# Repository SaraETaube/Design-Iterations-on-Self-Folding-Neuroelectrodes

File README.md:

# Design-Iterations-on-Self-Folding-Neuroelectrodes

The following files have been made available: 
- Project Report: Sara Taube_Design Iterations on Neuroelectrodes.pdf
- Project Poster: Sara Taube_final poster.pdf
- Project files:
    1. Electrode Design Files: in 1-electrode_design >
       final electrode slider.stl : printing file for electrode
       final electrode slider-SAP.stl : printing file for the SAP on electrode
       final electrode.ipt : Autodesk Inventor project file
    2. Applicator Design Files: in 2-surgical_implantation >
       hook_applicator_slide in.stl : printing file for applicator
       hook_applicator_slide in.ipt : Autodesk Inventor project file for applicator
       5 nerve model
       >  5 nerve model.stl : printing file for nerve model
       >  5 nerve model.ipt : Autodesk Inventor project file for nerve model
    3. Flexible Tether Design Files: in 3-flexible_tethers >
       long flex with bend : folder for KiCad Project files
       short flex with bend : folder for KiCad Project files
       spiral flex : folder for KiCad Project files
    4. Additional Design Files I created for Lukas during the internship: in 4-additional_stuff >
       fpc_connector_18pinOmnetics : folder for KiCad Project files for a connector PCB FPC-18pin Omnetics
       fpc_connector_36pinOmnetics : folder for KiCad Project files for a connector PCB FPC-36pin Omnetics
       Glas_Fiber_PCB : folder for KiCad Project files for a separate glas fiber project Lukas was doing
       USB_18pinOmnetics_bend : folder for KiCad Project files for a connector PCB USB-18pin Omnetics; bend for spacial efficacy
       USB_36pinOmnetics_straight : folder for KiCad Project files for a connector PCB USB-18pin Omnetics; no bend
       USB_18pinOmnetics_bend : folder for KiCad Project files for a connector PCB USB-36pin Omnetics; bend for spacial efficacy
       USB_36pinOmnetics_straight : folder for KiCad Project files for a connector PCB USB-36pin Omnetics; no bend

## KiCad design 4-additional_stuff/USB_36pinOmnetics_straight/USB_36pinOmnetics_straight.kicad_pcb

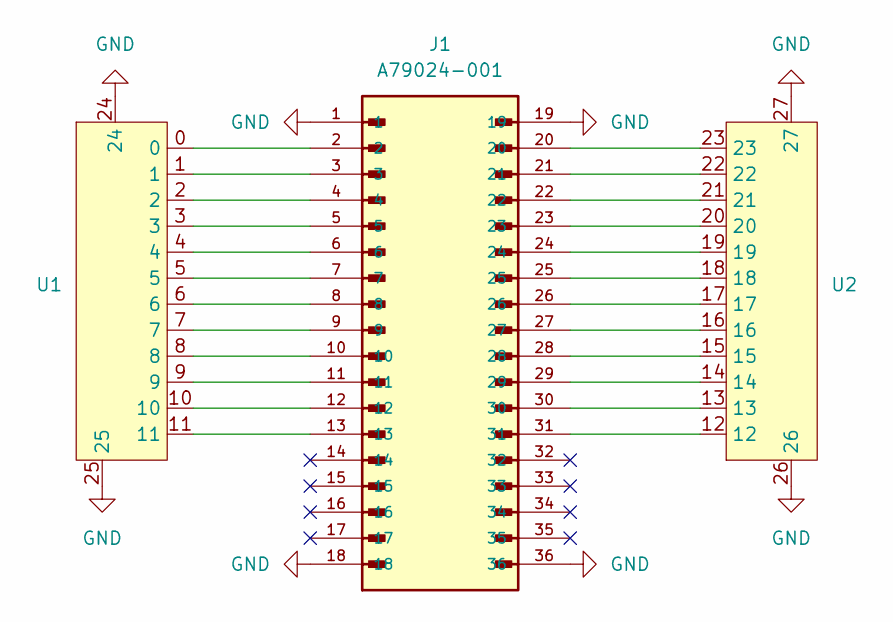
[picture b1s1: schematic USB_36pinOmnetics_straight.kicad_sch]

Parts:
J1: A79024-001; OMNETICS_A79024-001; PARTREV D
U1: 699C124-2A6-111 USB Plug_first half
U2: 699C124-2A6-111 USB Plug_second half

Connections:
GND: J1.1, J1.18, J1.19, J1.36, U1.24, U1.25, U2.26, U2.27
unnamed: J1.2, U1.0
unnamed: J1.3, U1.1
unnamed: J1.4, U1.2
unnamed: J1.5, U1.3
unnamed: J1.6, U1.4
unnamed: J1.7, U1.5
unnamed: J1.8, U1.6
unnamed: J1.9, U1.7
unnamed: J1.10, U1.8
unnamed: J1.11, U1.9
unnamed: J1.12, U1.10
unnamed: J1.13, U1.11
unnamed: J1.20, U2.23
unnamed: J1.21, U2.22
unnamed: J1.22, U2.21
unnamed: J1.23, U2.20
unnamed: J1.24, U2.19
unnamed: J1.25, U2.18
unnamed: J1.26, U2.17
unnamed: J1.27, U2.16
unnamed: J1.28, U2.15
unnamed: J1.29, U2.14
unnamed: J1.30, U2.13
unnamed: J1.31, U2.12

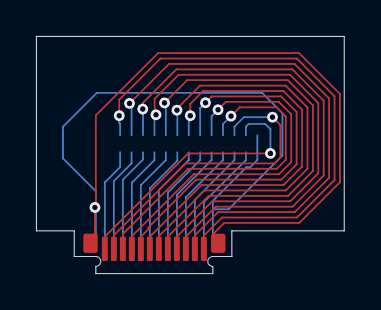
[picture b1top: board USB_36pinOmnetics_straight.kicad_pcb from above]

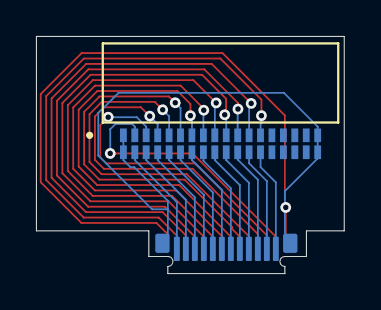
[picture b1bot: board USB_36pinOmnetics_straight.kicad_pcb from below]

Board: 2 copper layers, 17.1 x 13.2 mm, 3 parts (2 on the bottom side), 25 nets.

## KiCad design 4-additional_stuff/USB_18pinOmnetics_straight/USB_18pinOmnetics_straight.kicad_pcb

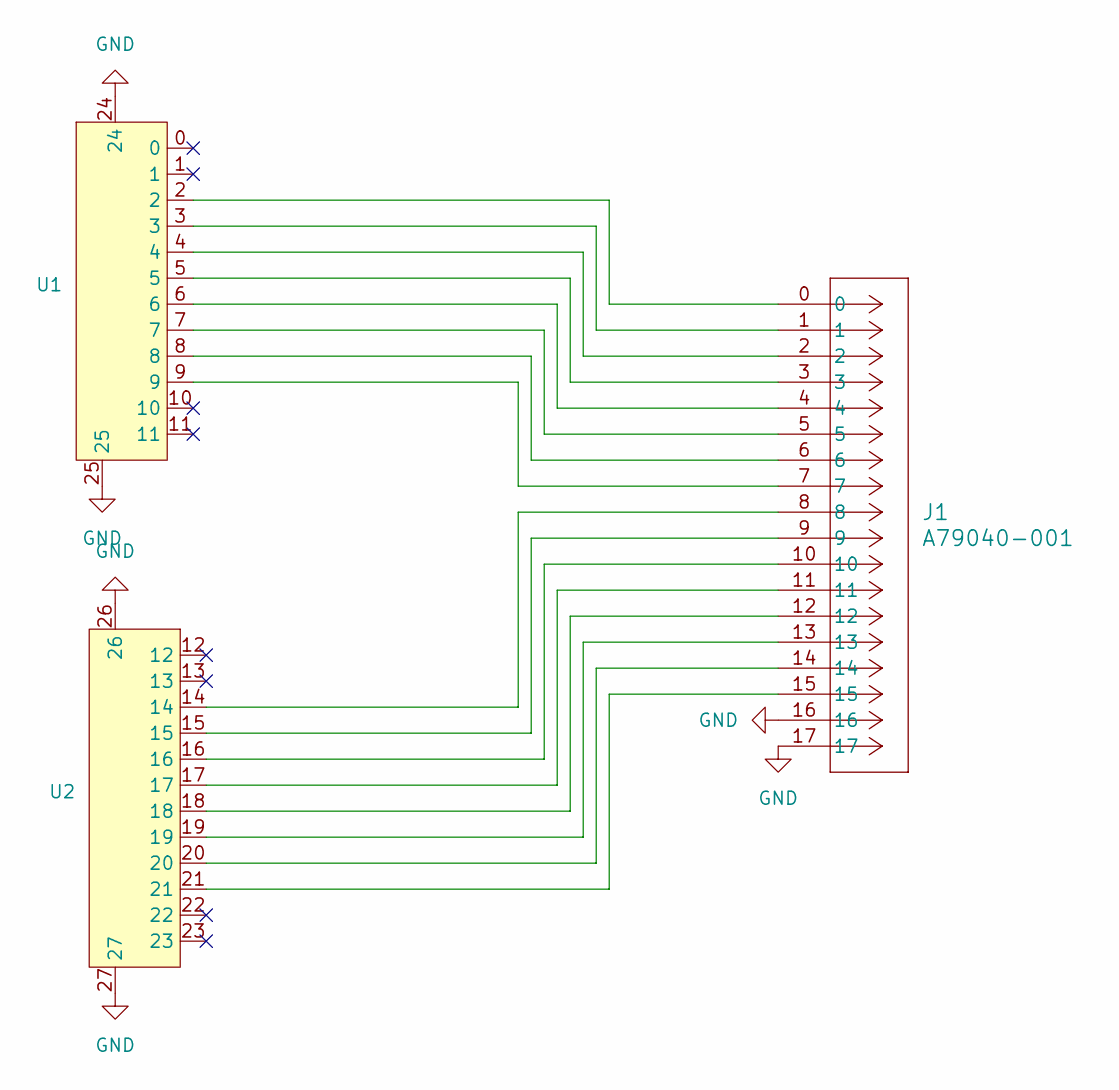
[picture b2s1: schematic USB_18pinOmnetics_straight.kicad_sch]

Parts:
J1: A79040-001; CONN18_NPD-18-AA_OMN
U1: 699C124-2A6-111 USB Plug_first half
U2: 699C124-2A6-111 USB Plug_second half

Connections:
GND: J1.16, J1.17, U1.24, U1.25, U2.26, U2.27
unnamed: J1.0, U1.2
unnamed: J1.1, U1.3
unnamed: J1.2, U1.4
unnamed: J1.3, U1.5
unnamed: J1.4, U1.6
unnamed: J1.5, U1.7
unnamed: J1.6, U1.8
unnamed: J1.7, U1.9
unnamed: J1.8, U2.14
unnamed: J1.9, U2.15
unnamed: J1.10, U2.16
unnamed: J1.11, U2.17
unnamed: J1.12, U2.18
unnamed: J1.13, U2.19
unnamed: J1.14, U2.20
unnamed: J1.15, U2.21

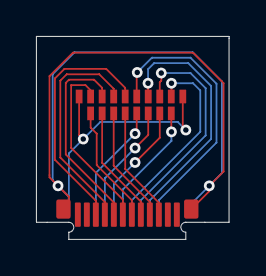
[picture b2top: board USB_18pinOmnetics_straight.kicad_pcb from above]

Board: 2 copper layers, 10.7 x 11.3 mm, 3 parts (1 on the bottom side), 17 nets.

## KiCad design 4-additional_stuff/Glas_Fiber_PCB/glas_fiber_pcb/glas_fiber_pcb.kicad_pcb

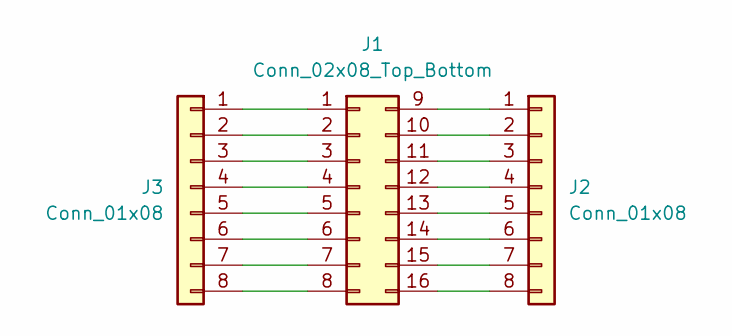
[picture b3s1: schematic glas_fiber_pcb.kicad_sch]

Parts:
J1: Conn_02x08_Top_Bottom; bondpads
J2, J3: Conn_01x08; PinHeader_1x08_P2.54mm_Vertical

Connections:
unnamed: J1.1, J3.1
unnamed: J1.2, J3.2
unnamed: J1.3, J3.3
unnamed: J1.4, J3.4
unnamed: J1.5, J3.5
unnamed: J1.6, J3.6
unnamed: J1.7, J3.7
unnamed: J1.8, J3.8
unnamed: J1.9, J2.1
unnamed: J1.10, J2.2
unnamed: J1.11, J2.3
unnamed: J1.12, J2.4
unnamed: J1.13, J2.5
unnamed: J1.14, J2.6
unnamed: J1.15, J2.7
unnamed: J1.16, J2.8

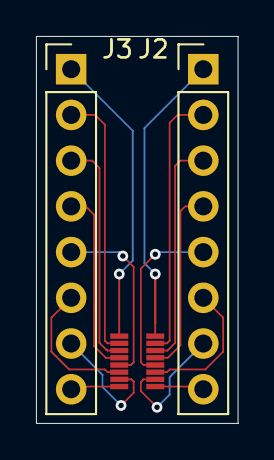
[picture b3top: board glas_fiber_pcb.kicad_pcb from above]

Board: 2 copper layers, 11.2 x 21.5 mm, 3 parts (0 on the bottom side), 16 nets.

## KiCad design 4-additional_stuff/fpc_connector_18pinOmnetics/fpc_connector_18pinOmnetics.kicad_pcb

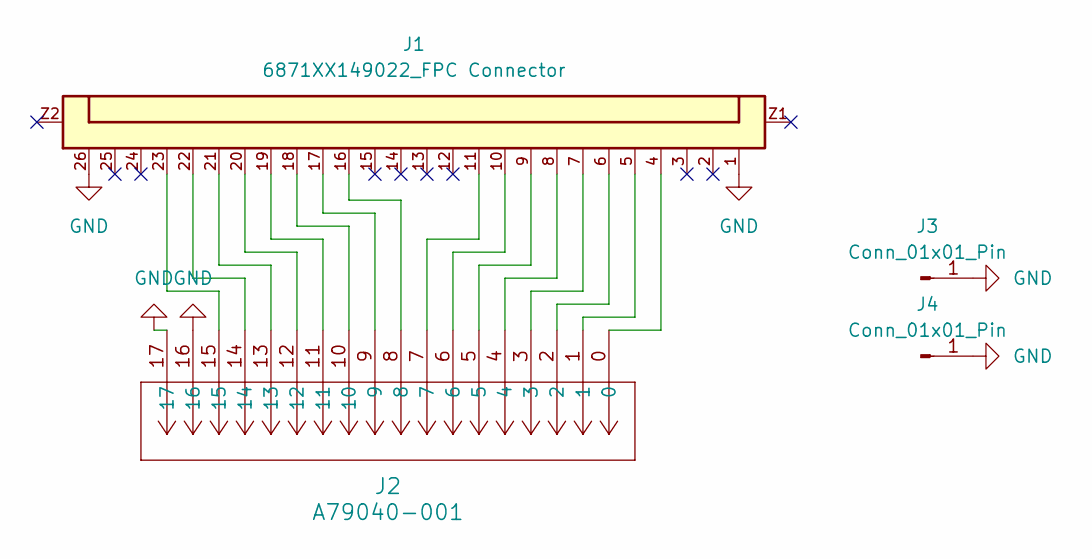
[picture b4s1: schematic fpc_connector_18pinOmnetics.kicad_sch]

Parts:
J1: 6871XX149022_FPC Connector; FPC_Connector_687126149022
J2: A79040-001; CONN18_NPD-18-AA_OMN
J3, J4: Conn_01x01_Pin; PinHeader_1x01_P2.54mm_Vertical

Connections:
GND: J1.1, J1.26, J2.16, J2.17, J3.1, J4.1
unnamed: J1.4, J2.0
unnamed: J1.5, J2.1
unnamed: J1.6, J2.2
unnamed: J1.7, J2.3
unnamed: J1.8, J2.4
unnamed: J1.9, J2.5
unnamed: J1.10, J2.6
unnamed: J1.11, J2.7
unnamed: J1.16, J2.8
unnamed: J1.17, J2.9
unnamed: J1.18, J2.10
unnamed: J1.19, J2.11
unnamed: J1.20, J2.12
unnamed: J1.21, J2.13
unnamed: J1.22, J2.14
unnamed: J1.23, J2.15

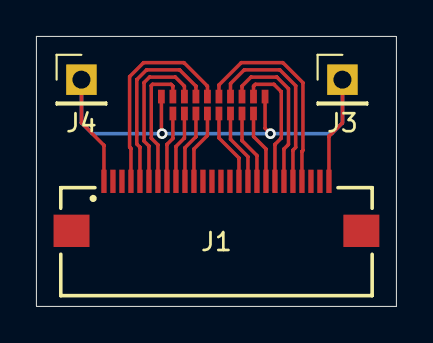
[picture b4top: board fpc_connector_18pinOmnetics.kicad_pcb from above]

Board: 2 copper layers, 20.0 x 15.0 mm, 4 parts (0 on the bottom side), 17 nets.

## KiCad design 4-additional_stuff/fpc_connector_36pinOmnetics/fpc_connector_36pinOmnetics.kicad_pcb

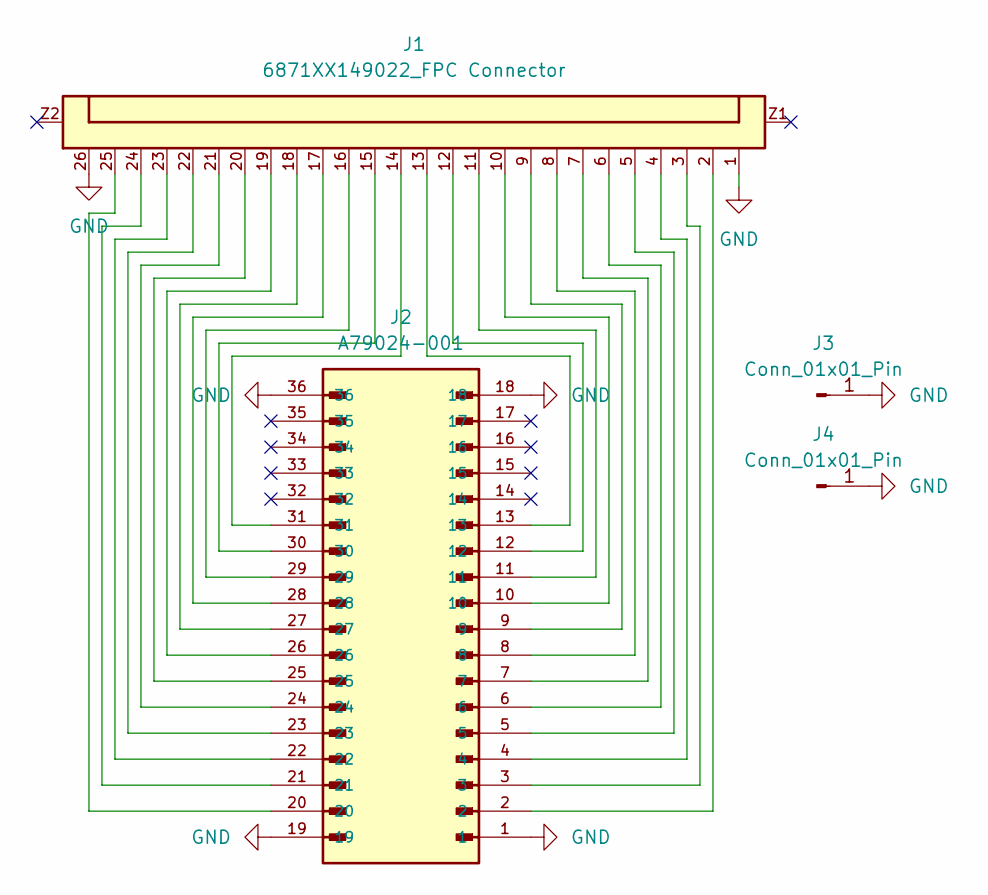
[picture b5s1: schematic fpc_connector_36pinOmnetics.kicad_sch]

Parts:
J1: 6871XX149022_FPC Connector; FPC_Connector_687126149022
J2: A79024-001; OMNETICS_A79024-001; PARTREV D
J3, J4: Conn_01x01_Pin; PinHeader_1x01_P2.54mm_Vertical

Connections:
GND: J1.1, J1.26, J2.1, J2.18, J2.19, J2.36, J3.1, J4.1
unnamed: J1.2, J2.2
unnamed: J1.3, J2.3
unnamed: J1.4, J2.4
unnamed: J1.5, J2.5
unnamed: J1.6, J2.6
unnamed: J1.7, J2.7
unnamed: J1.8, J2.8
unnamed: J1.9, J2.9
unnamed: J1.10, J2.10
unnamed: J1.11, J2.11
unnamed: J1.12, J2.12
unnamed: J1.13, J2.13
unnamed: J1.14, J2.31
unnamed: J1.15, J2.30
unnamed: J1.16, J2.29
unnamed: J1.17, J2.28
unnamed: J1.18, J2.27
unnamed: J1.19, J2.26
unnamed: J1.20, J2.25
unnamed: J1.21, J2.24
unnamed: J1.22, J2.23
unnamed: J1.23, J2.22
unnamed: J1.24, J2.21
unnamed: J1.25, J2.20

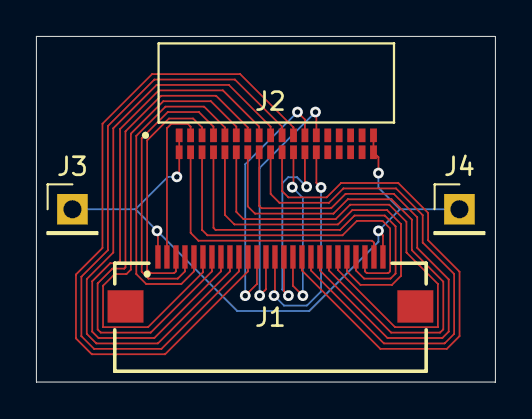
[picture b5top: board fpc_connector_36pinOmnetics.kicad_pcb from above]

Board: 2 copper layers, 25.5 x 19.2 mm, 4 parts (0 on the bottom side), 25 nets.

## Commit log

2026-02-15 project file details
    Added detailed descriptions of project files and their purposes.
